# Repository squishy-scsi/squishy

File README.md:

# Squishy: The SCSI Multitool

> [!IMPORTANT]
> Development for Squishy has been moved to [Codeberg](https://codeberg.org/Squishy/squishy) at [https://codeberg.org/Squishy/squishy](https://codeberg.org/Squishy/squishy). We look forward to your contributions there!

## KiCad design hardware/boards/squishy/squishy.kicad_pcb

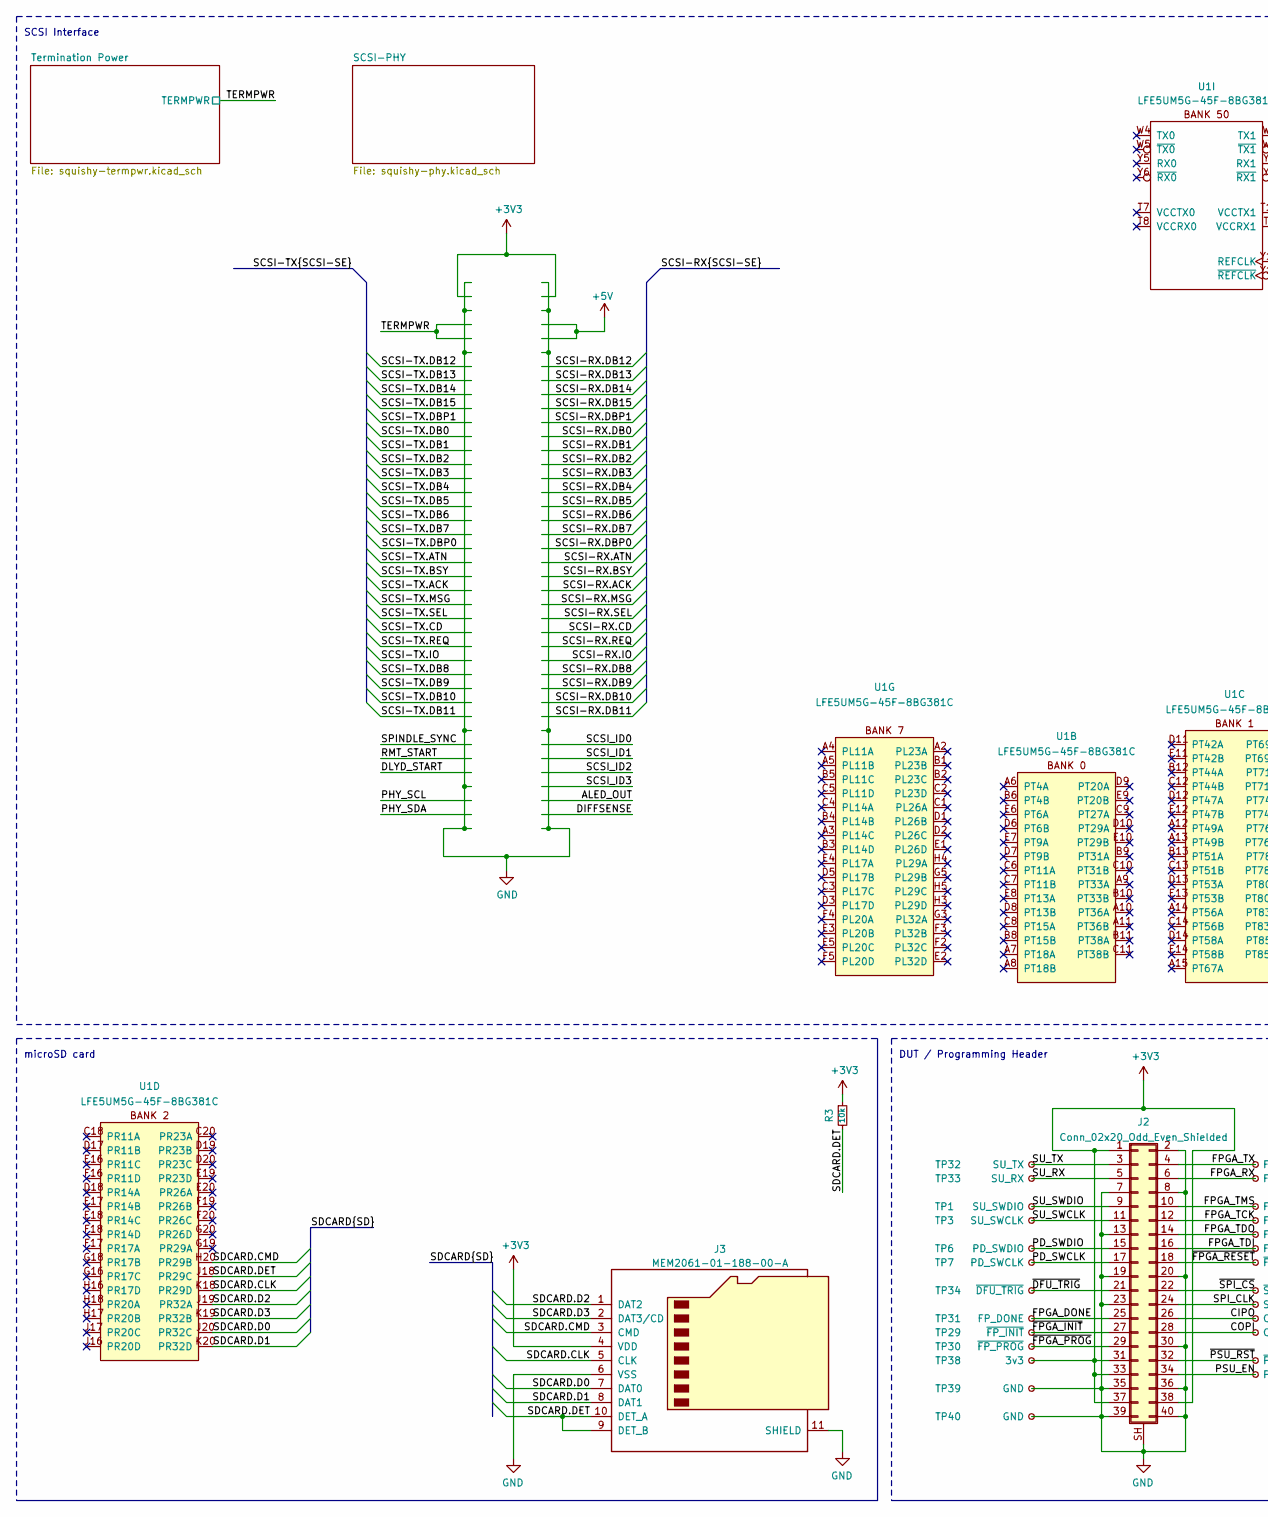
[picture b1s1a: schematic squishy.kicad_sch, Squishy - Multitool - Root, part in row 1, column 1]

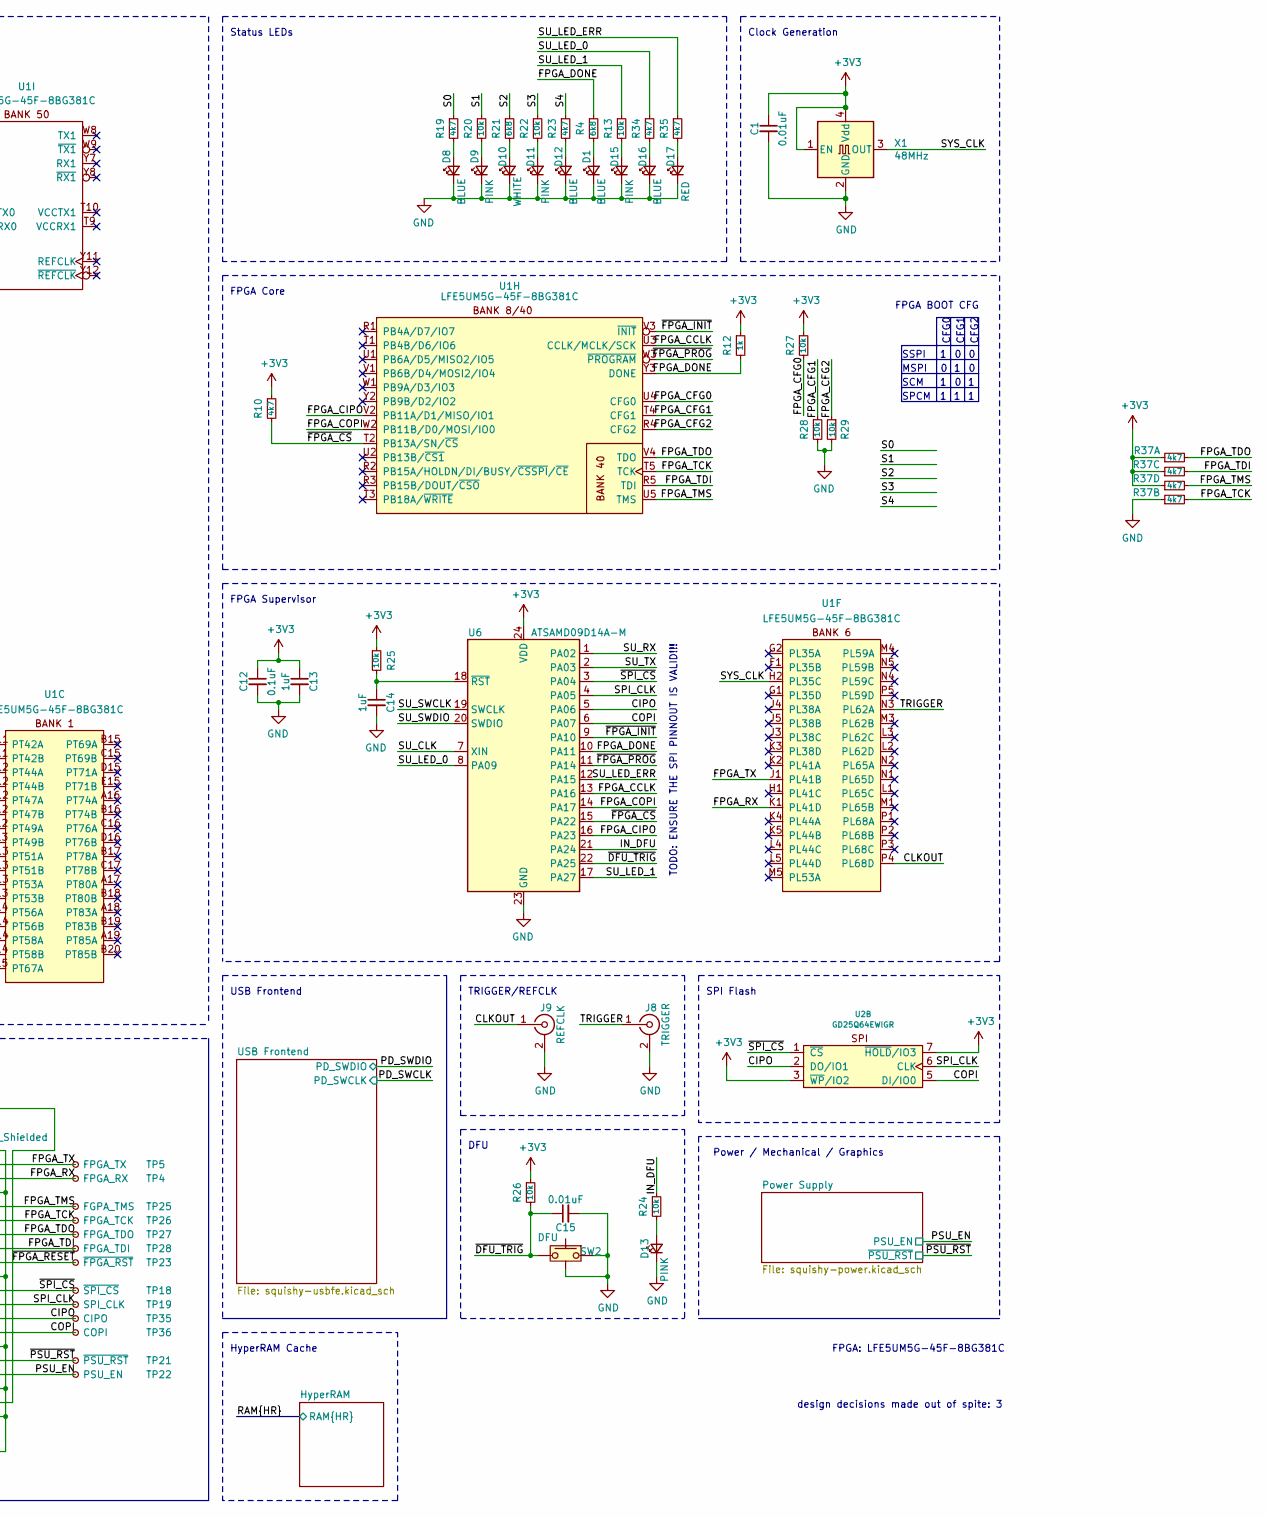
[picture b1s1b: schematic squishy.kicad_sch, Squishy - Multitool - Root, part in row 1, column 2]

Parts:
C1, C15: 0.01uF; C_0603_1608Metric; MPN C0402C103K3RACTU
C12: 0.1uF; C_0603_1608Metric; MPN C0402C104M8PACTU
C13, C14: 1uF; C_0603_1608Metric; MPN UMK107BJ105KA-T
D1, D8, D12, D16: BLUE; LED_0603_1608Metric_Pad1.05x0.95mm_HandSolder; MPN 150060BS75000
D9, D11, D13, D15: PINK; LED_0603_1608Metric_Pad1.05x0.95mm_HandSolder; MPN OSK40603C1E
D10: WHITE; LED_0603_1608Metric_Pad1.05x0.95mm_HandSolder; MPN SMLEN3WBC8W1
D17: RED; LED_0603_1608Metric_Pad1.05x0.95mm_HandSolder
J2: Conn_02x20_Odd_Even_Shielded; LSHM-120-01-L-RH-A-S-TR; MPN LSHM-120-01-L-RH-A-S-TR
J3: MEM2061-01-188-00-A; GCT_MEM2061-01-188-00-A_REVA; MPN MEM2061-01-188-00-A
J8: TRIGGER; Molex_SMA_732512120; MPN 732512120
J9: REFCLK; Molex_SMA_732512120; MPN 732512120
R3, R13, R20, R22, R24, R25, R26, R27, R28, R29: 10k; R_0603_1608Metric; MPN CRCW060310K0FKEA
R4: 6k8; R_0603_1608Metric
R10: 4k7; R_0603_1608Metric
R12: 1k; R_0603_1608Metric
R19, R23, R34, R35: 4k7; R_0603_1608Metric; MPN CRCW06034K70FKEA
R21: 6k8; R_0603_1608Metric; MPN CRCW06036K80FKEA
R37: 4k7; R0603_Array_Concave_4
SW2: DFU; SW_Tactile_SPST_Angled_TC-1109DE; MPN TC-1109DE-C-D
TP1: SU_SWDIO; TestPoint_Pad_D1.0mm; MPN N/A
TP3: SU_SWCLK; TestPoint_Pad_D1.0mm; MPN N/A
TP4: FPGA_RX; TestPoint_Pad_D1.0mm; MPN N/A
TP5: FPGA_TX; TestPoint_Pad_D1.0mm; MPN N/A
TP6: PD_SWDIO; TestPoint_Pad_D1.0mm; MPN N/A
TP7: PD_SWCLK; TestPoint_Pad_D1.0mm; MPN N/A
TP18: ~{SPI_CS}; TestPoint_Pad_D1.0mm; MPN N/A
TP19: SPI_CLK; TestPoint_Pad_D1.0mm; MPN N/A
TP21: ~{PSU_RST}; TestPoint_Pad_D1.0mm; MPN N/A
TP22: PSU_EN; TestPoint_Pad_D1.0mm; MPN N/A
TP23: ~{FPGA_RST}; TestPoint_Pad_D1.0mm; MPN N/A
TP25: FGPA_TMS; TestPoint_Pad_D1.0mm; MPN N/A
TP26: FPGA_TCK; TestPoint_Pad_D1.0mm; MPN N/A
TP27: FPGA_TDO; TestPoint_Pad_D1.0mm; MPN N/A
TP28: FPGA_TDI; TestPoint_Pad_D1.0mm; MPN N/A
TP29: ~{FP_INIT}; TestPoint_Pad_D1.0mm; MPN N/A
TP30: ~{FP_PROG}; TestPoint_Pad_D1.0mm; MPN N/A
TP31: FP_DONE; TestPoint_Pad_D1.0mm; MPN N/A
TP32: SU_TX; TestPoint_Pad_D1.0mm; MPN N/A
TP33: SU_RX; TestPoint_Pad_D1.0mm; MPN N/A
TP34: ~{DFU_TRIG}; TestPoint_Pad_D1.0mm; MPN N/A
TP35: CIPO; TestPoint_Pad_D1.0mm; MPN N/A
TP36: COPI; TestPoint_Pad_D1.0mm; MPN N/A
TP38: 3v3; TestPoint_Pad_D1.0mm; MPN N/A
TP39, TP40: GND; TestPoint_Pad_D1.0mm; MPN N/A
U1: LFE5UM5G-45F-8BG381C; 318caBGA; MPN LFE5UM5G-45F-8BG381C
U2: GD25Q64EWIGR; UDFN-8-1EP_6x5mm_P1.27mm_EP3.4x4mm; MPN GD25Q64EWIGR
U6: ATSAMD09D14A-M; QFN-24-1EP_4x4mm_P0.5mm_EP2.6x2.6mm; MPN ATSAMD09D14A-MUT
X1: 48MHz; SMD3225; MPN ASE-48.000MHZ-LC-T

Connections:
+3V3: C1.1, C12.1, C13.1, J2.1, J2.31, J2.33, J2.37, J2.38, J3.4 (VDD), R3.1, R10.1, R12.1, R25.1, R26.1, R27.1, R37.1, R37.5, R37.7, TP38.1, U2.3 (~WP/IO2), U2.7 (~HOLD/IO3), U6.24 (VDD), X1.1 (EN), X1.4 (Vdd); also elsewhere on the board
/CIPO: J2.26, TP35.1, U2.2 (DO/IO1), U6.5 (PA06)
/CLKOUT: J9.1 (In), U1.P4 (PL68D)
/COPI: J2.28, TP36.1, U2.5 (DI/IO0), U6.6 (PA07)
/FPGA_CCLK: U1.U3 (CCLK/MCLK/SCK), U6.13 (PA16)
/FPGA_CFG0: R27.2, U1.U4 (CFG0)
/FPGA_CFG1: R28.1, U1.T4 (CFG1)
/FPGA_CFG2: R29.1, U1.R4 (CFG2)
/FPGA_CIPO: U1.V2 (PB11A/D1/MISO/IO1), U6.16 (PA23)
/FPGA_COPI: U1.W2 (PB11B/D0/MOSI/IO0), U6.14 (PA17)
/FPGA_DONE: J2.25, R4.1, R12.2, TP31.1, U1.Y3 (DONE), U6.10 (PA11)
/FPGA_RX: J2.6, TP4.1, U1.K1 (PL41D)
/FPGA_TCK: J2.12, R37.4, TP26.1, U1.T5 (TCK)
/FPGA_TDI: J2.16, R37.6, TP28.1, U1.R5 (TDI)
/FPGA_TDO: J2.14, R37.2, TP27.1, U1.V4 (TDO)
/FPGA_TMS: J2.10, R37.8, TP25.1, U1.U5 (TMS)
/FPGA_TX: J2.4, TP5.1, U1.J1 (PL41B)
/IN_DFU: R24.1, U6.21 (PA24)
/PD_SWCLK: J2.17, TP7.1; also elsewhere on the board
/PD_SWDIO: J2.15, TP6.1; also elsewhere on the board
/PSU_EN: J2.34, TP22.1; also elsewhere on the board
/S0: R19.1
/S1: R20.1
/S2: R21.1
/S3: R22.1
/S4: R23.1
/SDCARD.CLK: J3.5 (CLK), U1.K18 (PR29D)
/SDCARD.CMD: J3.3 (CMD), U1.H20 (PR29B)
/SDCARD.D0: J3.7 (DAT0), U1.J20 (PR32C)
/SDCARD.D1: J3.8 (DAT1), U1.K20 (PR32D)
/SDCARD.D2: J3.1 (DAT2), U1.J19 (PR32A)
/SDCARD.D3: J3.2 (DAT3/CD), U1.K19 (PR32B)
/SDCARD.DET: J3.9 (DET_B), J3.10 (DET_A), R3.2, U1.J18 (PR29C)
/SPI_CLK: J2.24, TP19.1, U2.6 (CLK), U6.4 (PA05)
/SU_CLK: U6.7 (XIN)
/SU_LED_0: R34.1, U6.8 (PA09)
/SU_LED_1: R13.1, U6.17 (PA27)
/SU_LED_ERR: R35.1, U6.12 (PA15)
/SU_RX: J2.5, TP33.1, U6.1 (PA02)
/SU_SWCLK: J2.11, TP3.1, U6.19 (SWCLK)
/SU_SWDIO: J2.9, TP1.1, U6.20 (SWDIO)
/SU_TX: J2.3, TP32.1, U6.2 (PA03)
/SYS_CLK: U1.H2 (PL35C), X1.3 (OUT)
/TRIGGER: J8.1 (In), U1.N3 (PL62A)
/~DFU_TRIG: C15.1, J2.21, R26.2, SW2.2, TP34.1, U6.22 (PA25)
/~FPGA_CS: R10.2, U1.T2 (PB13A/SN/~CS), U6.15 (PA22)
/~FPGA_INIT: J2.27, TP29.1, U1.V3 (~INIT), U6.9 (PA10)
/~FPGA_PROG: J2.29, TP30.1, U1.W3 (~PROGRAM), U6.11 (PA14)
/~FPGA_RESET: J2.18, TP23.1
/~PSU_RST: J2.32, TP21.1; also elsewhere on the board
/~SPI_CS: J2.22, TP18.1, U2.1 (~CS), U6.3 (PA04)
unnamed: D1.2 (A), R4.2
unnamed: D8.2 (A), R19.2
unnamed: D9.2 (A), R20.2
unnamed: D10.2 (A), R21.2
unnamed: D11.2 (A), R22.2
unnamed: D12.2 (A), R23.2
unnamed: D13.2 (A), R24.2
unnamed: D15.2 (A), R13.2
unnamed: D16.2 (A), R34.2
unnamed: D17.2 (A), R35.2
unnamed: C14.1, R25.2, U6.18 (~RST)

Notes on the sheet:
FPGA BOOT CFG
SCSI Interface
TODO: ENSURE THE SPI PINNOUT IS VALID!!!
Power / Mechanical / Graphics
Status LEDs
FPGA Supervisor
SCM
MSPI
SPCM
FPGA: LFE5UM5G-45F-8BG381C
Clock Generation
DFU
design decisions made out of spite: 3
SPI Flash
USB Frontend
CFG2
microSD card
FPGA Core
CFG0
CFG1
SSPI
HyperRAM Cache
DUT / Programming Header
TRIGGER/REFCLK

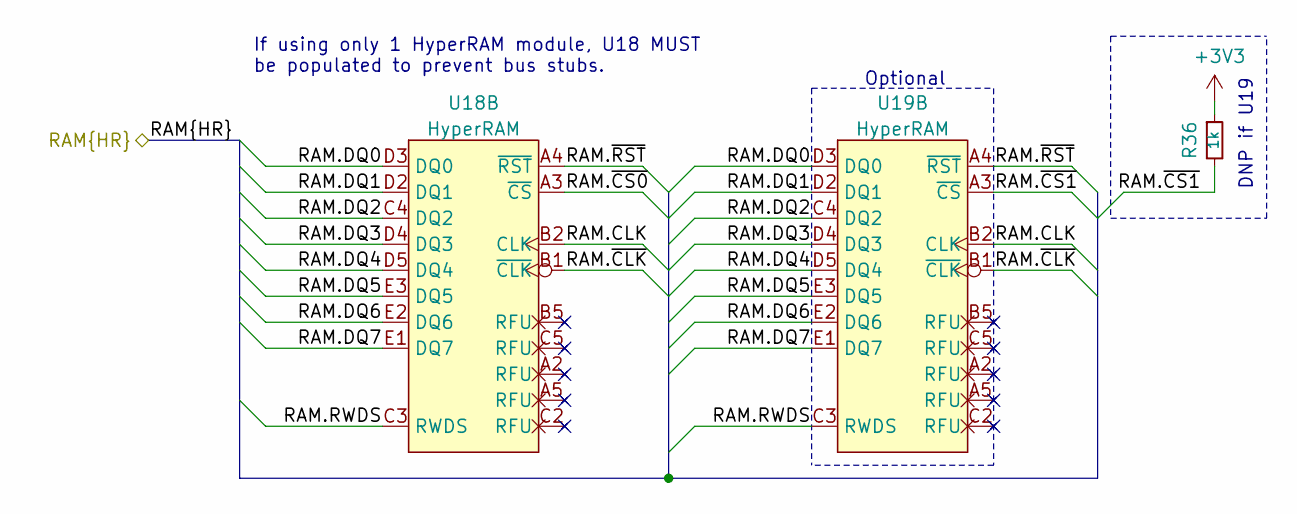
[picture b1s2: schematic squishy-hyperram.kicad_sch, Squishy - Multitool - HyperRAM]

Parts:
R36: 1k; R_0603_1608Metric
U18, U19: HyperRAM; TFBGA-24-6x8mm-1.0mm; MPN W956A8MBYA5I

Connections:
+3V3: R36.1; also elsewhere on the board
/RAM.CLK: U18.B2 (CLK), U19.B2 (CLK)
/RAM.DQ0: U18.D3 (DQ0), U19.D3 (DQ0)
/RAM.DQ1: U18.D2 (DQ1), U19.D2 (DQ1)
/RAM.DQ2: U18.C4 (DQ2), U19.C4 (DQ2)
/RAM.DQ3: U18.D4 (DQ3), U19.D4 (DQ3)
/RAM.DQ4: U18.D5 (DQ4), U19.D5 (DQ4)
/RAM.DQ5: U18.E3 (DQ5), U19.E3 (DQ5)
/RAM.DQ6: U18.E2 (DQ6), U19.E2 (DQ6)
/RAM.DQ7: U18.E1 (DQ7), U19.E1 (DQ7)
/RAM.RWDS: U18.C3 (RWDS), U19.C3 (RWDS)
/RAM.~CLK: U18.B1 (~CLK), U19.B1 (~CLK)
/RAM.~CS0: U18.A3 (~CS)
/RAM.~CS1: R36.2, U19.A3 (~CS)
/RAM.~RST: U18.A4 (~RST), U19.A4 (~RST)

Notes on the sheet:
Optional
If using only 1 HyperRAM module, U18 MUST be populated to prevent bus stubs.
DNP if U19

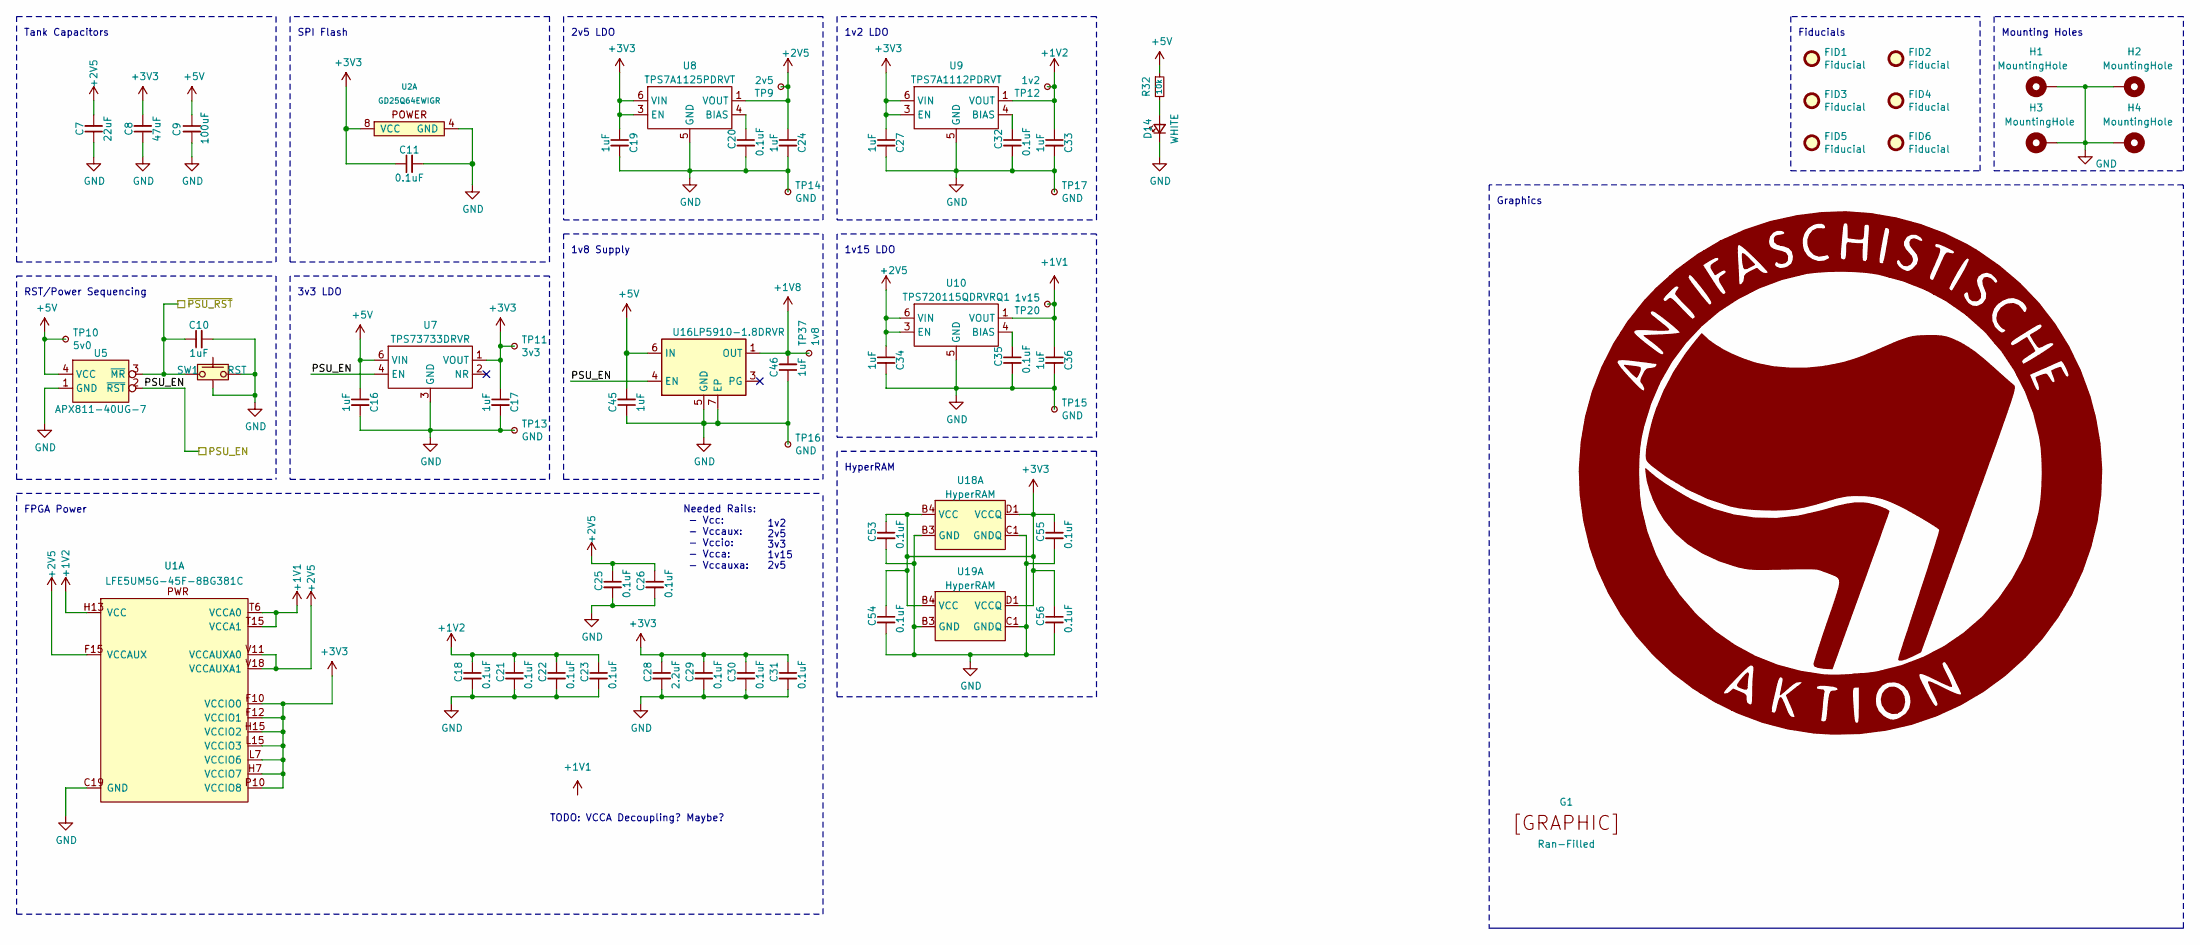
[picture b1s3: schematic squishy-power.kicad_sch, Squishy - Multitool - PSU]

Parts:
C7: 22uF; C_1210_3225Metric
C8: 47uF; C_1210_3225Metric; MPN EMK325ABJ476KMHP
C9: 100uF; C_1210_3225Metric; MPN C1210C107M4PAC7800
C10, C16, C17, C19, C24, C27, C33, C34, C36, C45, C46: 1uF; C_0603_1608Metric; MPN UMK107BJ105KA-T
C11: 0.1uF; C_0603_1608Metric; MPN C0402C104M8PACTU
C18, C20, C21, C22, C23, C25, C26, C29, C30, C31, C32, C35, C53, C54, C55, C56: 0.1uF; C_0402_1005Metric
C28: 2.2uF; C_0603_1608Metric
D14: WHITE; LED_0603_1608Metric_Pad1.05x0.95mm_HandSolder; MPN SMLEN3WBC8W1
FID1, FID2, FID3, FID4, FID5, FID6: Fiducial; Fiducial_0.75mm_Mask1.5mm; MPN N/A
G1: Ran-Filled; yuki_10x11; MPN N/A
G2: Antifaschistische_Aktion; Antifaschistische-Aktion_Inv_600dpi; MPN N/A
H1, H2, H3, H4: MountingHole; MountingHole_3.2mm_M3_Pad; MPN N/A
R32: 10k; R_0603_1608Metric; MPN CRCW06036K80FKEA
SW1: RST; SW_Tactile_SPST_Angled_TC-1109DE; MPN TC-1109DE-C-D
TP9: 2v5; TestPoint_Pad_D1.0mm; MPN N/A
TP10: 5v0; TestPoint_Pad_D1.0mm; MPN N/A
TP11: 3v3; TestPoint_Pad_D1.0mm; MPN N/A
TP12: 1v2; TestPoint_Pad_D1.0mm; MPN N/A
TP13, TP14, TP15, TP16, TP17: GND; TestPoint_Pad_D1.0mm; MPN N/A
TP20: 1v15; TestPoint_Pad_D1.0mm; MPN N/A
TP37: 1v8; TestPoint_Pad_D1.0mm; MPN N/A
U1: LFE5UM5G-45F-8BG381C; 318caBGA; MPN LFE5UM5G-45F-8BG381C
U2: GD25Q64EWIGR; UDFN-8-1EP_6x5mm_P1.27mm_EP3.4x4mm; MPN GD25Q64EWIGR
U5: APX811-40UG-7; SOT-143; MPN APX811-40UG-7
U7: TPS73733DRVR; WSON-6-1EP_2x2mm_P0.65mm_EP1x1.6mm; MPN TPS73733DRVR
U8: TPS7A1125PDRVT; WSON-6-1EP_2x2mm_P0.65mm_EP1x1.6mm; MPN TPS7A1125PDRVT
U9: TPS7A1112PDRVT; WSON-6-1EP_2x2mm_P0.65mm_EP1x1.6mm; MPN TPS7A1112PDRVT
U10: TPS720115QDRVRQ1; WSON-6-1EP_2x2mm_P0.65mm_EP1x1.6mm; MPN TPS720115QDRVRQ1
U16: LP5910-1.8DRVR; WSON-6-1EP_2x2mm_P0.65mm_EP1x1.6mm_ThermalVias; MPN LP5910-1.8DRVR
U18, U19: HyperRAM; TFBGA-24-6x8mm-1.0mm; MPN W956A8MBYA5I

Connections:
+1V1: C36.1, TP20.1, U1.T6 (VCCA0), U1.T15 (VCCA1), U1.U6 (VCCA0), U1.U15 (VCCA1), U10.1 (VOUT), U10.2 (NC)
+1V2: C18.1, C21.1, C22.1, C23.1, C33.1, TP12.1, U1.H8 (VCC), U1.H9 (VCC), U1.H10 (VCC), U1.H11 (VCC), U1.H12 (VCC), U1.H13 (VCC), U1.J8 (VCC), U1.J13 (VCC), U1.K8 (VCC), U1.K13 (VCC), U1.L8 (VCC), U1.L13 (VCC), U1.M8 (VCC), U1.M13 (VCC), U1.N8 (VCC), U1.N9 (VCC), U1.N10 (VCC), U1.N11 (VCC), U1.N12 (VCC), U1.N13 (VCC), U9.1 (VOUT), U9.2 (NC)
+1V8: C46.2, TP37.1, U16.1 (OUT); also elsewhere on the board
+2V5: C7.2, C24.1, C25.1, C26.1, C34.1, TP9.1, U1.F6 (VCCAUX), U1.F15 (VCCAUX), U1.P6 (VCCAUX), U1.P15 (VCCAUX), U1.V10 (VCCAUXA0), U1.V11 (VCCAUXA0), U1.V17 (VCCAUXA1), U1.V18 (VCCAUXA1), U8.1 (VOUT), U8.2 (NC), U10.3 (EN), U10.6 (VIN)
+3V3: C8.2, C11.1, C17.1, C19.1, C27.1, C28.1, C29.1, C30.1, C31.1, C53.1, C54.1, C55.1, C56.1, TP11.1, U1.F9 (VCCIO0), U1.F10 (VCCIO0), U1.F11 (VCCIO1), U1.F12 (VCCIO1), U1.H6 (VCCIO7), U1.H7 (VCCIO7), U1.H14 (VCCIO2), U1.H15 (VCCIO2), U1.J6 (VCCIO7), U1.J15 (VCCIO2), U1.L6 (VCCIO6), U1.L7 (VCCIO6), U1.L14 (VCCIO3), U1.L15 (VCCIO3), U1.M6 (VCCIO6), U1.M15 (VCCIO3), U1.P9 (VCCIO8), U1.P10 (VCCIO8), U2.8 (VCC), U7.1 (VOUT), U8.3 (EN), U8.6 (VIN), U9.3 (EN), U9.6 (VIN), U18.B4 (VCC), U18.D1 (VCCQ), U18.E4 (VCCQ), U19.B4 (VCC), U19.D1 (VCCQ), U19.E4 (VCCQ); also elsewhere on the board
+5V: C9.1, C16.1, C45.2, R32.1, TP10.1, U5.4 (VCC), U7.5 (NC), U7.6 (VIN), U16.6 (IN); also elsewhere on the board
/PSU_EN: U5.2 (~RST), U7.4 (EN), U16.4 (EN); also elsewhere on the board
/~PSU_RST: C10.1, SW1.1, U5.3 (~MR); also elsewhere on the board
unnamed: D14.2 (A), R32.2
unnamed: C20.1, U8.4 (BIAS)
unnamed: C32.1, U9.4 (BIAS)
unnamed: C35.1, U10.4 (BIAS)

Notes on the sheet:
RST/Power Sequencing
1v8 Supply
Fiducials
TODO: VCCA Decoupling? Maybe?
2v5
Needed Rails: - Vcc: - Vccaux: - Vccio: - Vcca: - Vccauxa:
3v3
FPGA Power
3v3 LDO
1v2
1v2 LDO
Tank Capacitors
SPI Flash
Graphics
1v15 LDO
1v15
Mounting Holes
2v5 LDO
HyperRAM

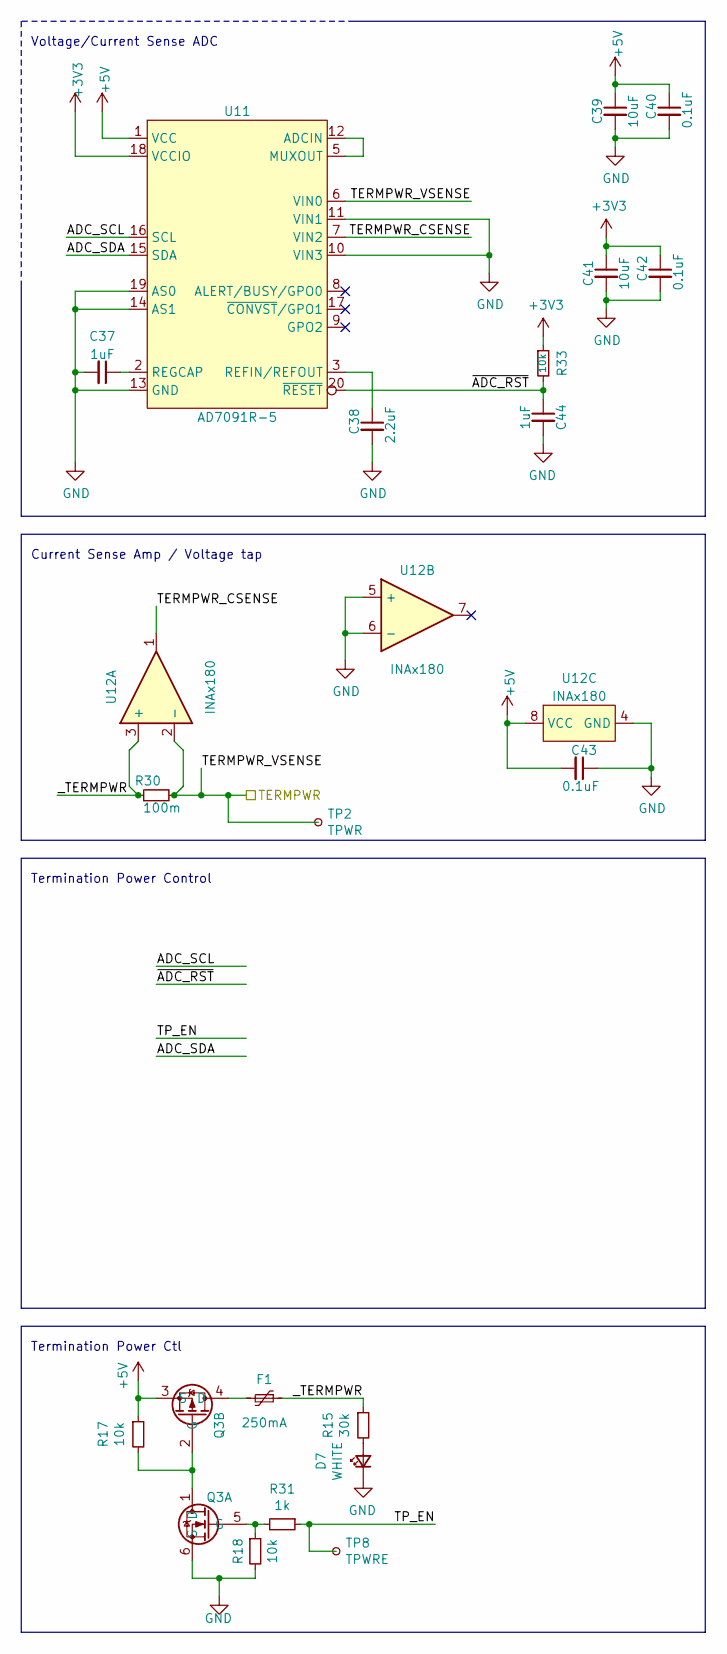
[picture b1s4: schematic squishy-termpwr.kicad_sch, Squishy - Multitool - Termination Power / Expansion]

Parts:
C37, C44: 1uF; C_0603_1608Metric; MPN UMK107BJ105KA-T
C38: 2.2uF; C_0603_1608Metric
C39, C41: 10uF; C_0603_1608Metric
C40, C42, C43: 0.1uF; C_0402_1005Metric
D7: WHITE; LED_0603_1608Metric_Pad1.05x0.95mm_HandSolder; MPN SMLEN3WBC8W1
F1: 250mA; Fuse_1210_3225Metric; MPN 0ZCH0050FF2G
Q3: Q_NMOS_PMOS_D1G2S2D2G1S1; X2-DFN1310-6; MPN DMC3730UFL3
R15: 30k; R_0603_1608Metric; MPN RC0603FR-0730KL
R17, R18, R33: 10k; R_0603_1608Metric; MPN CRCW060310K0FKEA
R30: 100m; R_0805_2012Metric
R31: 1k; R_0603_1608Metric
TP2: TPWR; TestPoint_Pad_D1.0mm; MPN N/A
TP8: TPWRE; TestPoint_Pad_D1.0mm; MPN N/A
U11: AD7091R-5; QFN-20-1EP_4x4mm_P0.5mm_EP2.5x2.5mm; MPN AD7091R-5BCPZ-RL7
U12: INAx180; WSON_8_2x2mm_1EP; MPN INA2180A3IDSGR

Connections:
+3V3: C41.1, C42.1, R33.1, U11.18 (VCCIO); also elsewhere on the board
+5V: C39.1, C40.1, C43.2, Q3.3 (S), R17.1, U11.1 (VCC), U12.8 (VCC); also elsewhere on the board
/TERMPWR: R30.2, TP2.1, U11.6 (VIN0), U12.2 (-)
/Termination Power/ADC_SCL: U11.16 (SCL)
/Termination Power/ADC_SDA: U11.15 (SDA)
/Termination Power/TERMPWR_CSENSE: U11.7 (VIN2), U12.1
/Termination Power/TP_EN: R31.1, TP8.1
/Termination Power/_TERMPWR: F1.1, R15.1, R30.1, U12.3 (+)
/Termination Power/~ADC_RST: C44.1, R33.2, U11.20 (~RESET)
unnamed: D7.2 (A), R15.2
unnamed: Q3.1 (D), Q3.2 (G), R17.2
unnamed: Q3.5 (G), R18.1, R31.2
unnamed: F1.2, Q3.4 (D)
unnamed: U11.5 (MUXOUT), U11.12 (ADCIN)
unnamed: C38.1, U11.3 (REFIN/REFOUT)
unnamed: C37.1, U11.2 (REGCAP)

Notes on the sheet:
Current Sense Amp / Voltage tap
Termination Power Control
Termination Power Ctl
Voltage/Current Sense ADC

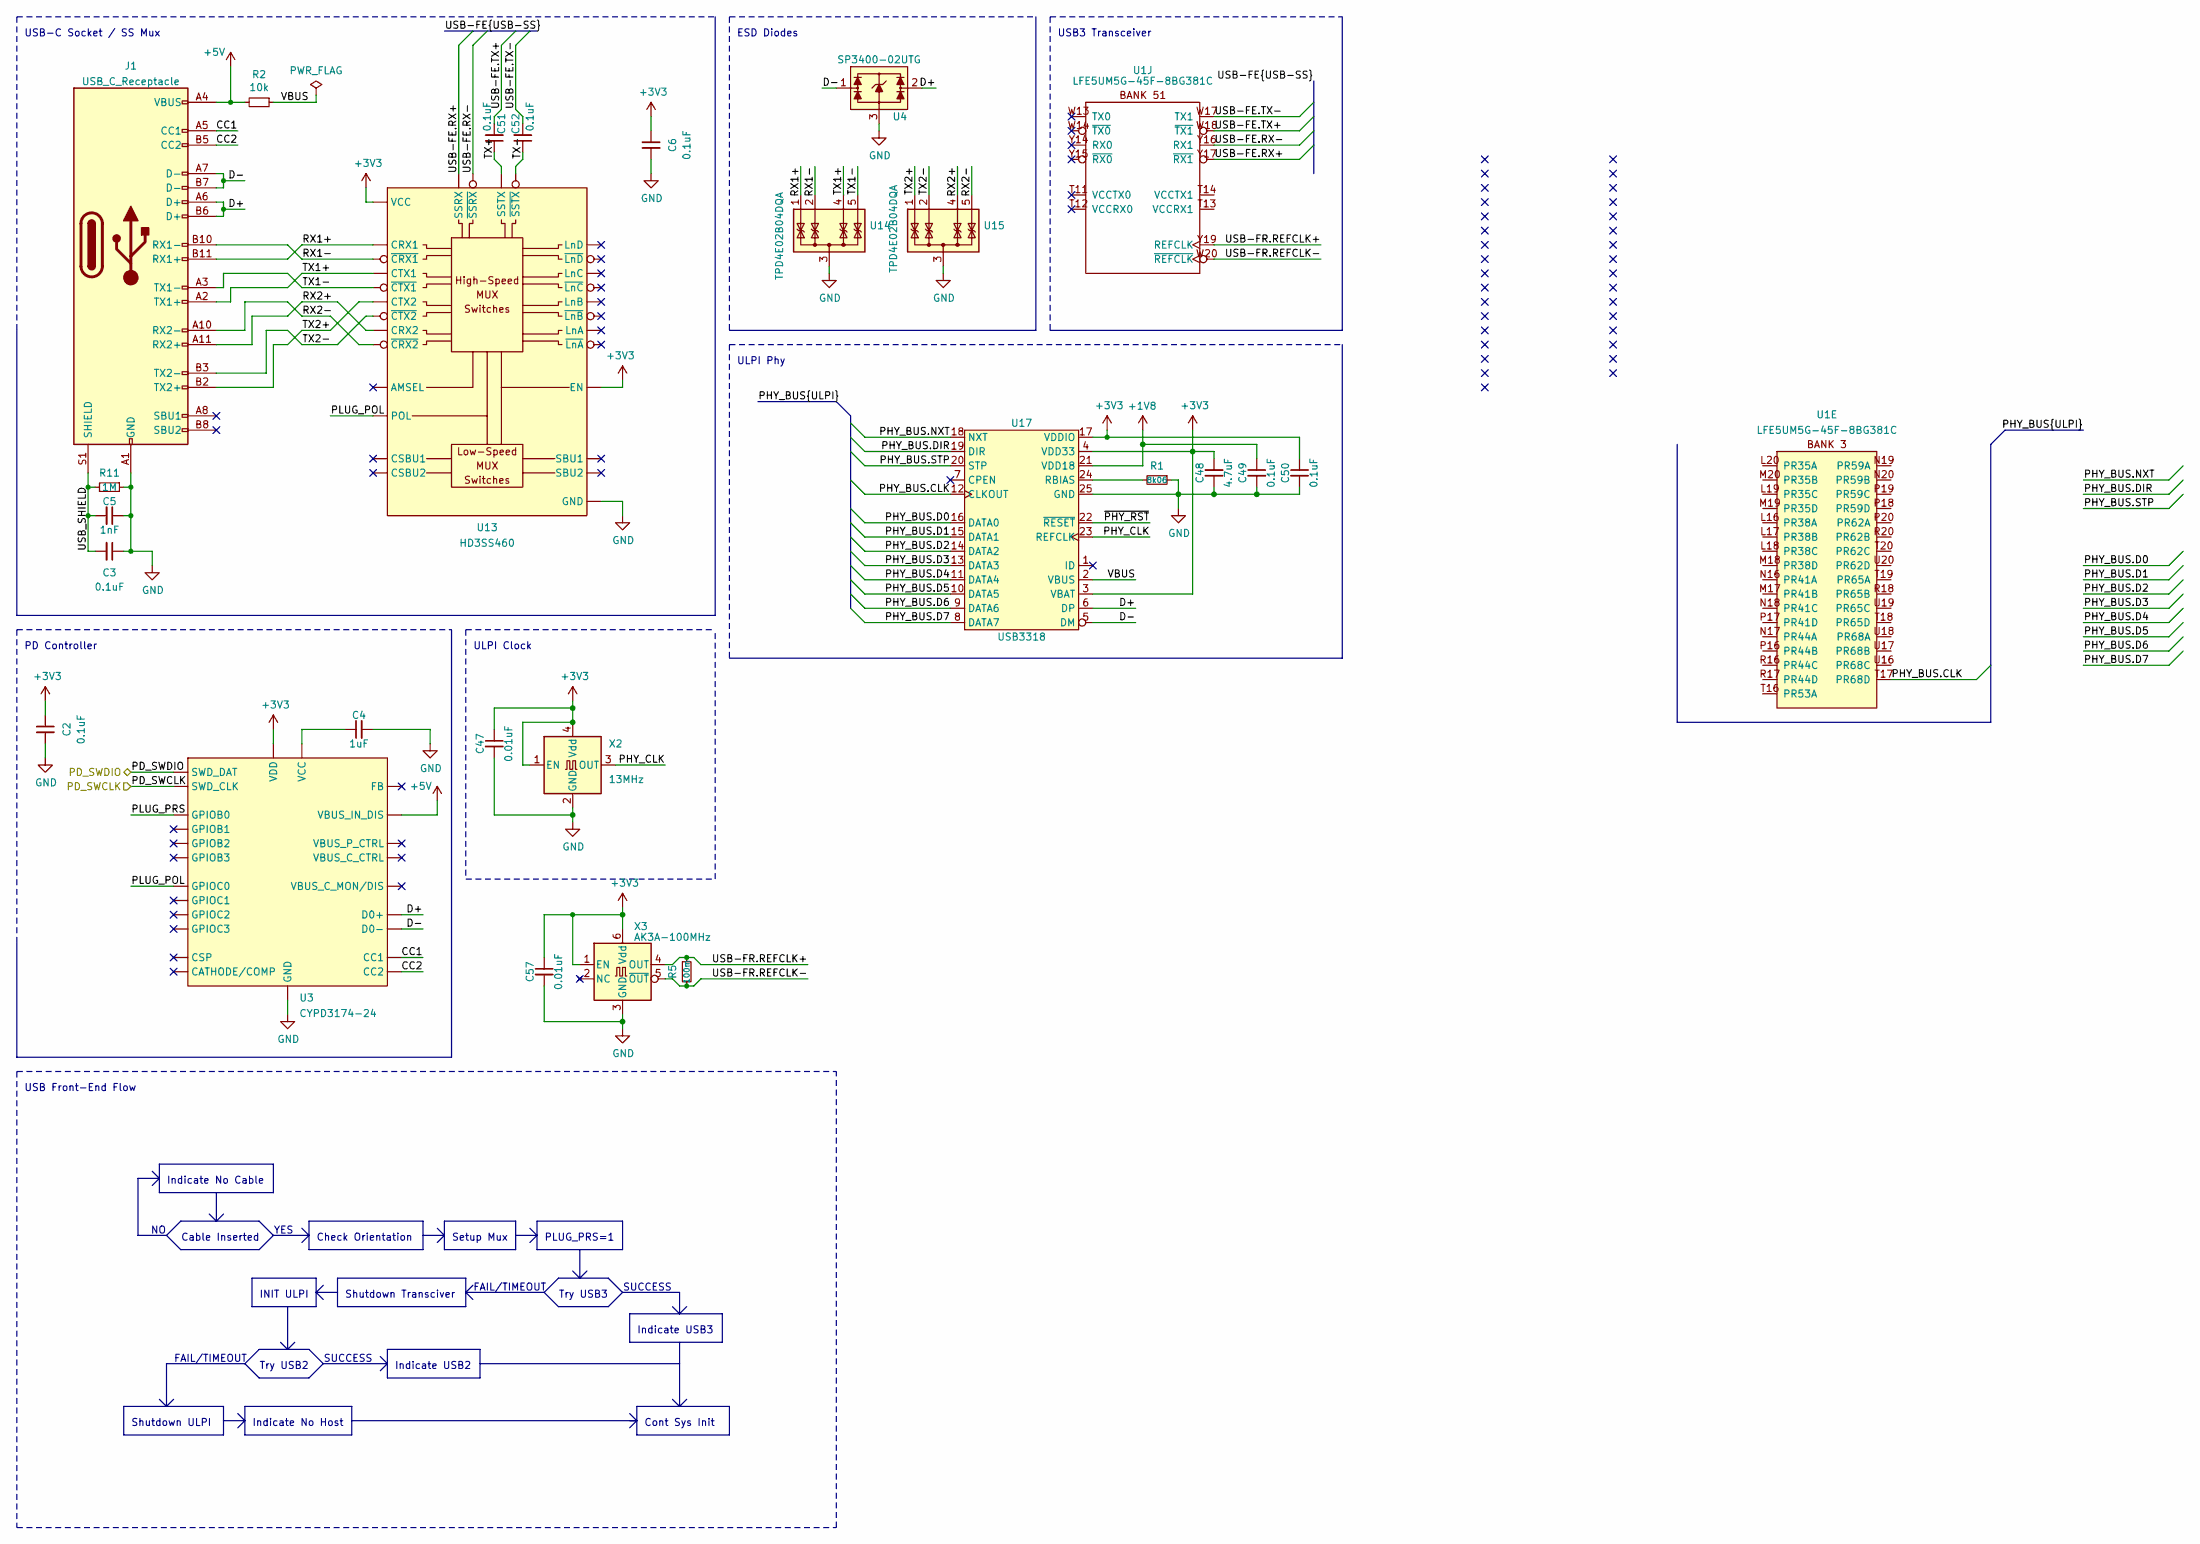
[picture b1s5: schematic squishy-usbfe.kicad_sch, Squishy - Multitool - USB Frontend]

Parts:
C2, C3, C6: 0.1uF; C_0603_1608Metric; MPN C0603C104M5RACTU
C4: 1uF; C_0603_1608Metric; MPN UMK107BJ105KA-T
C5: 1nF; C_0603_1608Metric
C47, C57: 0.01uF; C_0603_1608Metric; MPN C0402C103K3RACTU
C48: 4.7uF; C_0603_1608Metric; MPN C0603C475K8PACTU
C49, C50: 0.1uF; C_0603_1608Metric; MPN C0402C104M8PACTU
C51, C52: 0.1uF; C_0402_1005Metric
J1: USB_C_Receptacle; USB-3.1-Type-C_In-PCB; MPN 918-418K2022C40000
R1: 8k06; R_0603_1608Metric; MPN CRCW06038K06FKEAC
R2: 10k; R_0603_1608Metric; MPN CRCW060310K0FKEA
R5: 100m; R_0603_1608Metric
R11: 1M; R_0603_1608Metric; MPN CRCW06031M00FKEA
U1: LFE5UM5G-45F-8BG381C; 318caBGA; MPN LFE5UM5G-45F-8BG381C
U3: CYPD3174-24; QFN-24-1EP_4x4mm_P0.5mm_EP2.6x2.6mm; MPN (effects (font (size 1.27 1.27)) (justi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
U4: SP3400-02UTG; UDFN-6L; MPN SP3400-02UTG
U13: HD3SS460; WQFN-28-1EP_3.5x5.5_P0.5mm_EP2x4mm; MPN HD3SS460
U14, U15: TPD4E02B04DQA; USON-10_2.5x1.0mm_P0.5mm; MPN TPD4E02B04DQA
U17: USB3318; QFN-24-1EP_4x4mm_P0.5mm_EP2.6x2.6mm; MPN USB3318-CP-TR
X2: 13MHz; SMD3225
X3: AK3A-100MHz; AK3A-xxxMHz; MPN AK3ADDF1-100.000T3

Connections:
+1V8: C49.1, U17.21 (VDD18); also elsewhere on the board
+3V3: C2.1, C6.1, C47.1, C48.2, C50.1, C57.1, U3.23 (VDD), U13.17 (EN), U13.22 (VCC), U17.3 (VBAT), U17.4 (VDD33), U17.17 (VDDIO), X2.1 (EN), X2.4 (Vdd), X3.1 (EN), X3.6 (Vdd); also elsewhere on the board
+5V: J1.A4 (VBUS), J1.A9 (VBUS), J1.B4 (VBUS), J1.B9 (VBUS), R2.2, U3.18 (VBUS_IN_DIS); also elsewhere on the board
/PD_SWCLK: U3.8 (SWD_CLK); also elsewhere on the board
/PD_SWDIO: U3.7 (SWD_DAT); also elsewhere on the board
/USB Frontend/CC2: J1.B5 (CC2), U3.14 (CC2)
/USB Frontend/D+: J1.A6 (D+), J1.B6 (D+), U3.17 (D0+), U4.2 (IO2), U4.5 (NC), U17.6 (DP)
/USB Frontend/D-: J1.A7 (D-), J1.B7 (D-), U3.16 (D0-), U4.1 (IO1), U4.6 (NC), U17.5 (DM)
/USB Frontend/PHY_BUS.CLK: U1.T17 (PR68D), U17.12 (CLKOUT)
/USB Frontend/PHY_BUS.D0: U17.16 (DATA0)
/USB Frontend/PHY_BUS.D1: U17.15 (DATA1)
/USB Frontend/PHY_BUS.D2: U17.14 (DATA2)
/USB Frontend/PHY_BUS.D3: U17.13 (DATA3)
/USB Frontend/PHY_BUS.D4: U17.11 (DATA4)
/USB Frontend/PHY_BUS.D5: U17.10 (DATA5)
/USB Frontend/PHY_BUS.D6: U17.9 (DATA6)
/USB Frontend/PHY_BUS.D7: U17.8 (DATA7)
/USB Frontend/PHY_BUS.DIR: U17.19 (DIR)
/USB Frontend/PHY_BUS.NXT: U17.18 (NXT)
/USB Frontend/PHY_BUS.STP: U17.20 (STP)
/USB Frontend/PHY_CLK: U17.23 (REFCLK), X2.3 (OUT)
/USB Frontend/PLUG_POL: U3.9 (GPIOC0), U13.3 (POL)
/USB Frontend/PLUG_PRS: U3.1 (GPIOB0)
/USB Frontend/RX1+: J1.B11 (RX1+), U13.1 (CRX1), U14.1 (IO1), U14.10 (NC)
/USB Frontend/RX1-: J1.B10 (RX1-), U13.2 (~CRX1), U14.2 (IO2), U14.9 (NC)
/USB Frontend/RX2+: J1.A11 (RX2+), U13.9 (CRX2), U15.4 (IO3), U15.7 (NC)
/USB Frontend/RX2-: J1.A10 (RX2-), U13.10 (~CRX2), U15.5 (IO4), U15.6 (NC)
/USB Frontend/TX1+: J1.A2 (TX1+), U13.4 (CTX1), U14.4 (IO3), U14.7 (NC)
/USB Frontend/TX1-: J1.A3 (TX1-), U13.5 (~CTX1), U14.5 (IO4), U14.6 (NC)
/USB Frontend/TX2+: J1.B2 (TX2+), U13.6 (CTX2), U15.1 (IO1), U15.10 (NC)
/USB Frontend/TX2-: J1.B3 (TX2-), U13.7 (~CTX2), U15.2 (IO2), U15.9 (NC)
/USB Frontend/TX+: C51.1, U13.26 (SSTX)
/USB Frontend/TX-: C52.1, U13.25 (~SSTX)
/USB Frontend/USB-FE.RX+: U1.Y17 (~RX1), U13.28 (SSRX)
/USB Frontend/USB-FE.RX-: U1.Y16 (RX1), U13.27 (~SSRX)
/USB Frontend/USB-FE.TX+: C51.2, U1.W18 (~TX1)
/USB Frontend/USB-FE.TX-: C52.2, U1.W17 (TX1)
/USB Frontend/USB-FR.REFCLK+: R5.1, U1.Y19 (REFCLK), X3.4 (OUT)
/USB Frontend/USB-FR.REFCLK-: R5.2, U1.W20 (~REFCLK), X3.5 (~OUT)
/USB Frontend/USB_SHIELD: C3.2, C5.2, J1.S1 (SHIELD), R11.2
/USB Frontend/VBUS: R2.1, U17.2 (VBUS)
/USB Frontend/~PHY_RST: U17.22 (~RESET)
unnamed: C4.1, U3.24 (VCC)
unnamed: R1.2, U17.24 (RBIAS)

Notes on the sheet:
Indicate No Host
PLUG_PRS=1
FAIL/TIMEOUT
ESD Diodes
Cont Sys Init
ULPI Clock
Shutdown ULPI
YES
USB-C Socket / SS Mux
Check Orientation
SUCCESS
Indicate No Cable
PD Controller
Shutdown Transciver
Try USB2
ULPI Phy
Setup Mux
USB Front-End Flow
Cable Inserted
Indicate USB3
USB3 Transceiver
Indicate USB2
Try USB3
INIT ULPI

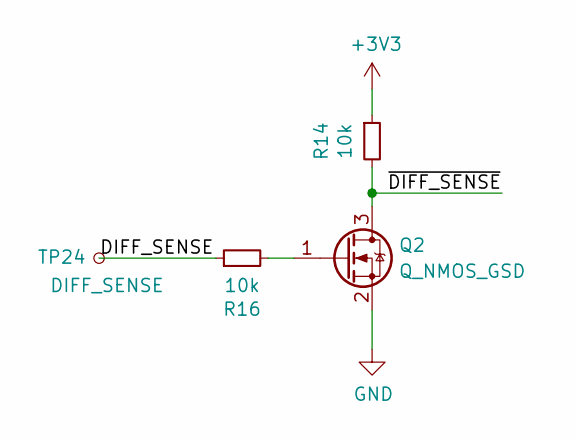
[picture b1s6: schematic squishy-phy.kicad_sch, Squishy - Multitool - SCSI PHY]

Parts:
Q2: Q_NMOS_GSD; SOT-23; MPN DMN65D8L-7
R14, R16: 10k; R_0603_1608Metric; MPN CRCW060310K0FKEA
TP24: DIFF_SENSE; TestPoint_Pad_D1.0mm; MPN N/A

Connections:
+3V3: R14.1; also elsewhere on the board
/SCSI-PHY/DIFF_SENSE: R16.1, TP24.1
/SCSI-PHY/~DIFF_SENSE: Q2.3 (D), R14.2
unnamed: Q2.1 (G), R16.2

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

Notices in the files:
firmware/spi.cc:
SPDX-License-Identifier: BSD-3-Clause
hardware/boards/squishy/squishy-hyperram.kicad_sch:
License:  CERN-OHL-S
© 2022 Aki 'lethalbit' Van Ness, et. al.
hardware/boards/squishy/squishy.kicad_pcb:
CERN-OHL-S
